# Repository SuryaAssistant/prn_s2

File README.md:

<!-- Title -->
<span align = "center">

# PRN
  <b>Bidirectional SMPS Inverter</b>

STM32 Code

September - December 2021

This repository is open to copy for Educational purpose only and not for commercial use

</span>
<!-- End of Title -->

## Warning
The code and OpenHantek software are produced in Linux OS computer. We recommend you to use or edit the code in Linux computer for compatibility purpose. Nevertheless, you still can use this repo in Windows computer with some configuration but not for OpenHantek.

## Brief Overview of The Repository
This repository is used to save and documenting the development of bidirectional SMPS inverter project. The project was took place in Instrumentation and Control Laboratory, Universitas Sebelas Maret.

## Prequerities
Yout need to have this software before use this repository
- STM32CubeIDE v1.6.1 or above. Link : https://www.st.com/en/development-tools/stm32cubeide.html
- OpenHantek6022 (Linux). Link : https://github.com/OpenHantek/OpenHantek6022
- Autodesk Eagle v9.3.0 or above (Linux or Windows). Link : https://www.autodesk.com/products/eagle/free-download

## How To Use (Linux)
From Terminal, clone this repository to your folder
```
git clone https://github.com/SuryaAssistant/prn_s2
```

Open STM32CubeIDE and then open project `prn_s2.ioc` in `stm32` folder.

The main code is saved in `stm32/Core/Src/main.c`.

## How To Use (Windows)
Download this repository by clicking green button in right-top of repository.

Extract the zip file and then move the `stm32` folder into <b>STM32CubeIDE workspace</b> in (usually) `C:\Users\{Your_Computer_Name}\STM32CubeIDE\{Your_Workspace_Name}\`.

## Clock Configuration
<span align="center">

</span>

## Pinout
<span align="center">

</span>

## Further Information
- Read the STM32CubeIDE timer and ADC configuration in https://github.com/SuryaAssistant/prn_s2/tree/main/tutorial
- Read SPWM specific configuration in https://github.com/SuryaAssistant/prn_s2/tree/main/spwm
- PCB schematic and board Design Documentation in https://github.com/SuryaAssistant/prn_s2/tree/main/pcb

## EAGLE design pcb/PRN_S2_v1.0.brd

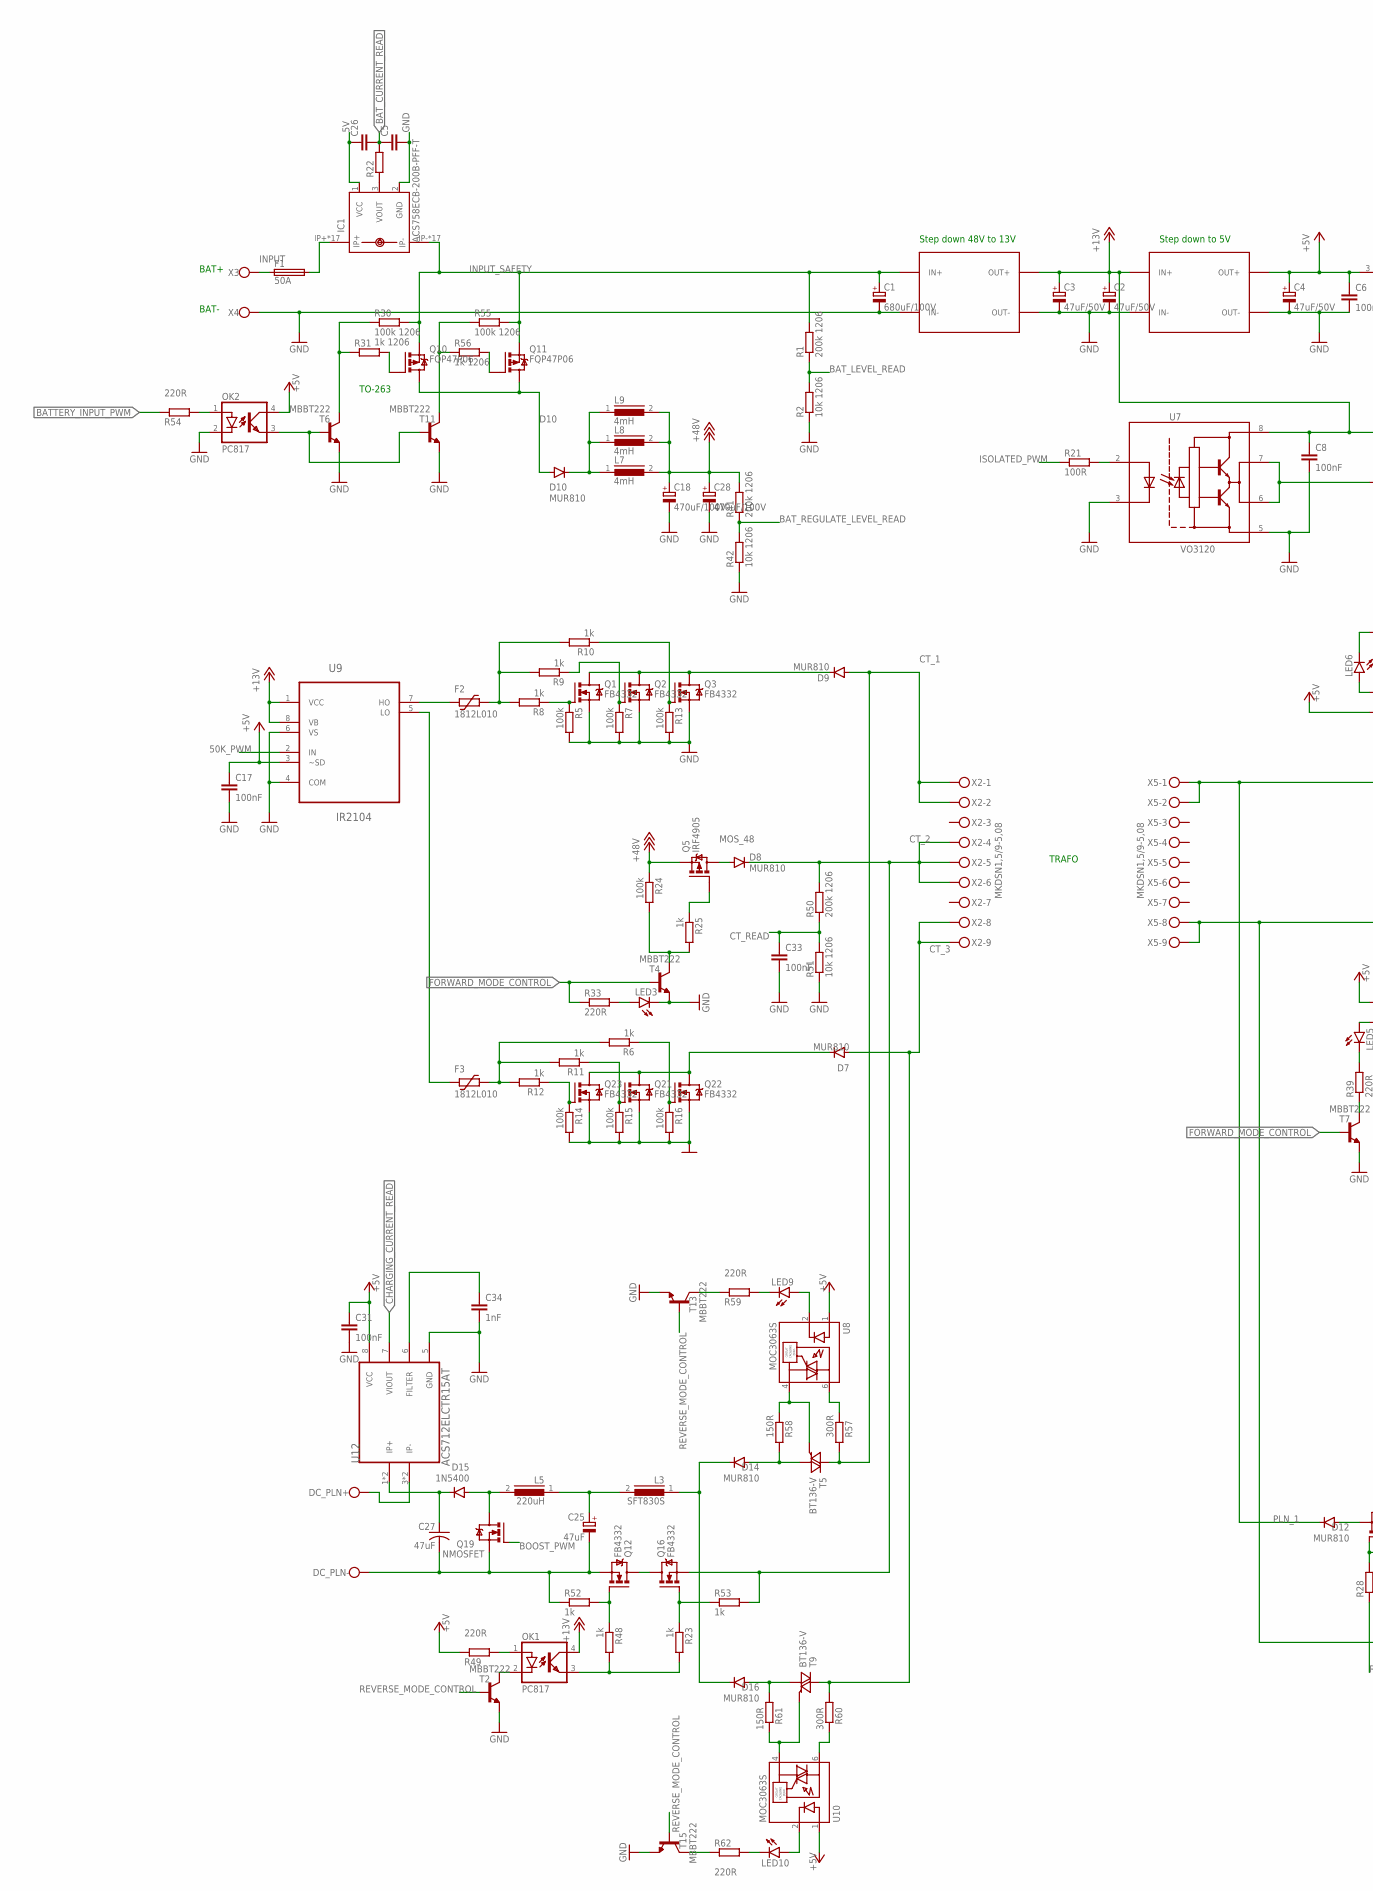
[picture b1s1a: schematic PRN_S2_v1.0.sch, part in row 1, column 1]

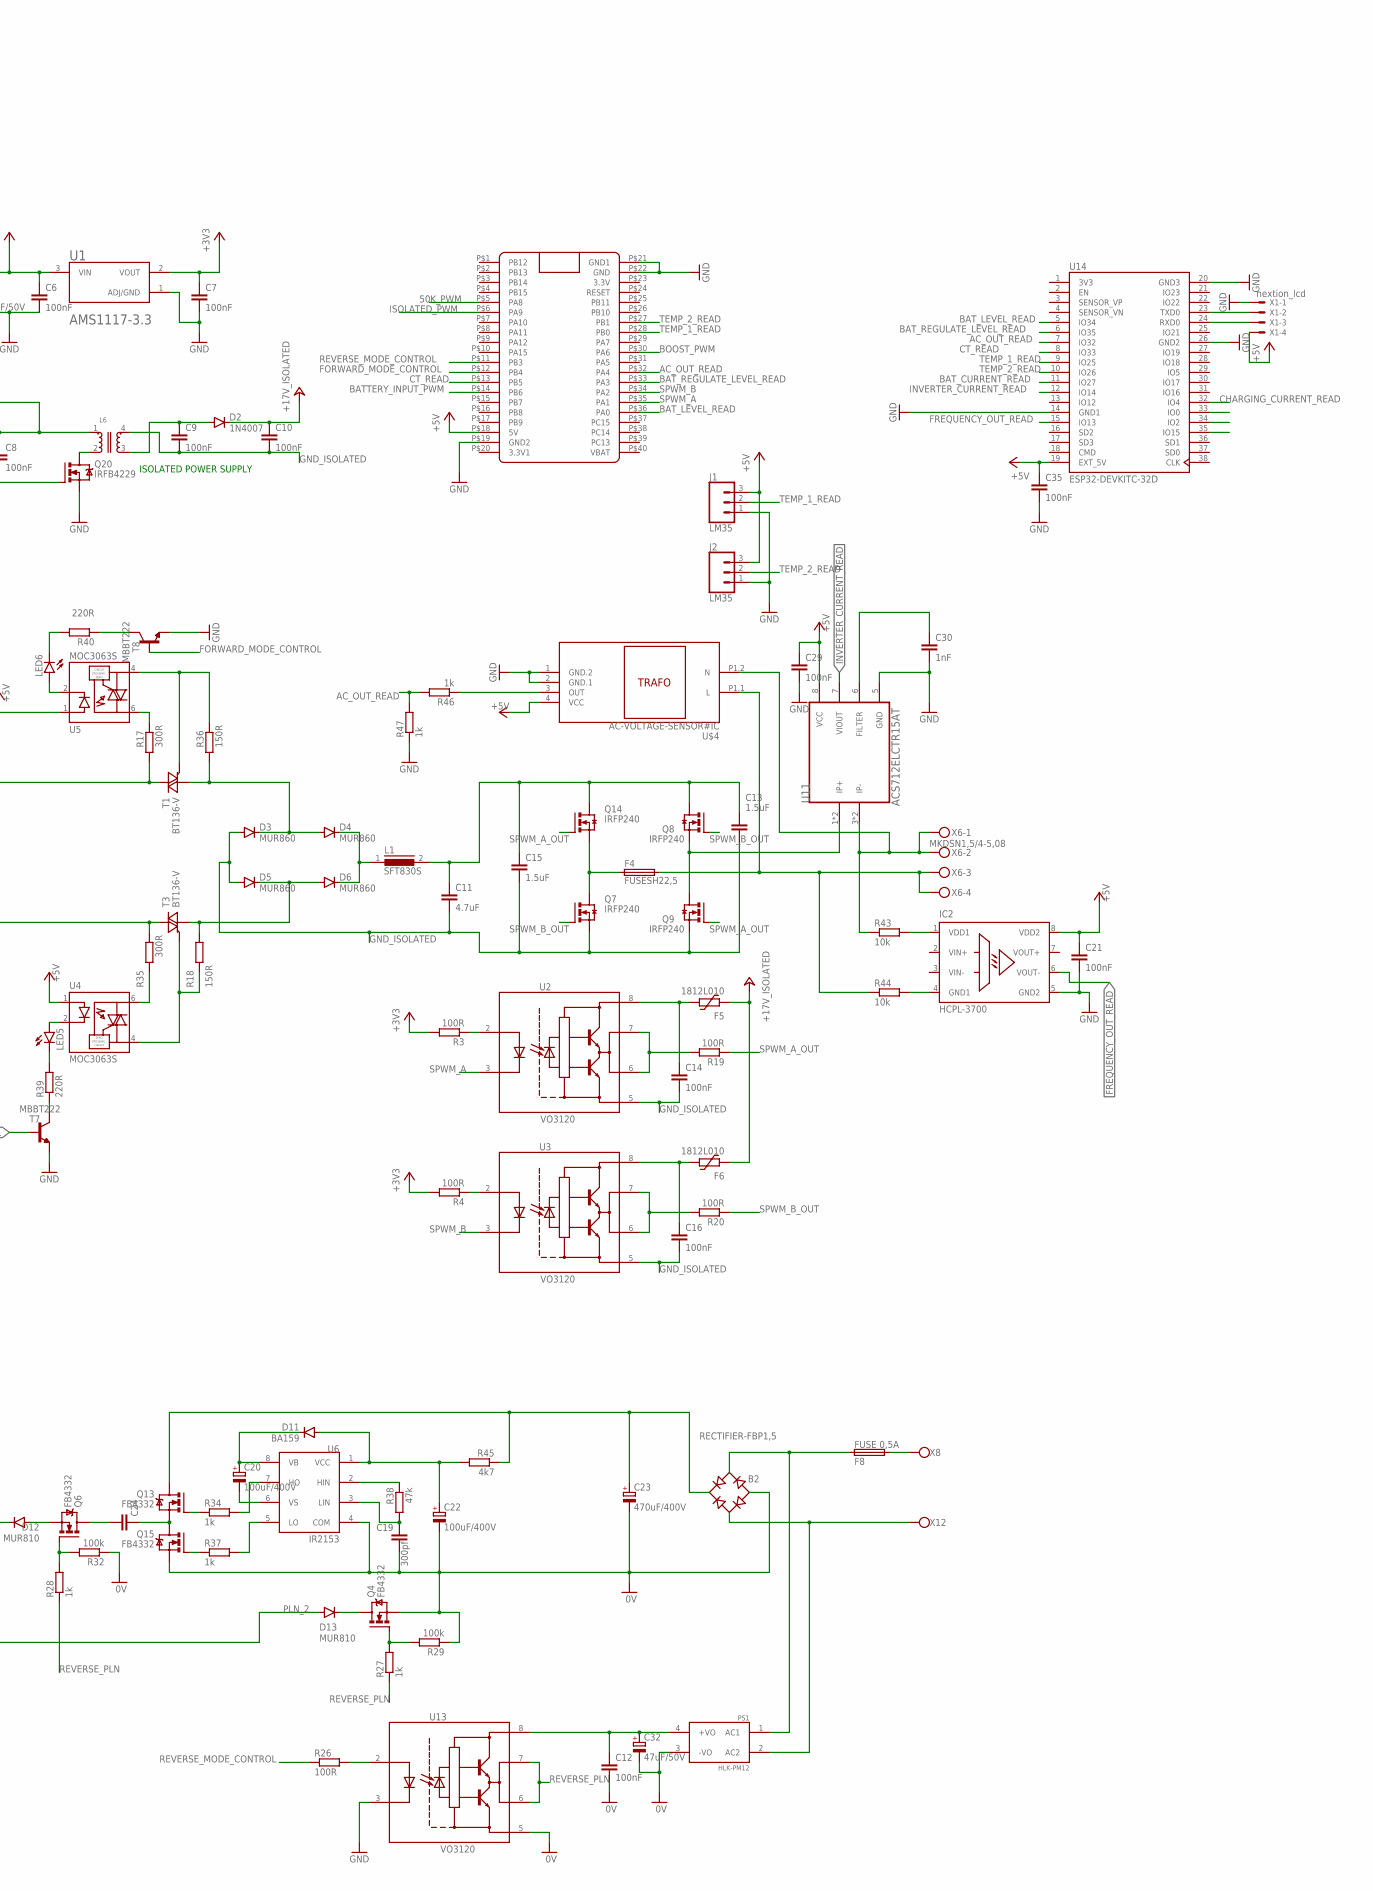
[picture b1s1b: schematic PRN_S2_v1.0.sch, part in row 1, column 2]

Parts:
B2: RECTIFIER-FBP1,5; FBP1,5
C1: 680uF/100V; E7,5-18
C2, C3, C4, C32: 47uF/50V; E2,5-6
C5, C26: CC0603; C0603
C6, C7, C14, C16, C17, C21, C29, C31, C35: 100nF; C0805K
C8, C9, C10, C12, C33: 100nF; C050-025X075
C11: 4.7uF; C275-113X316
C13, C15: 1.5uF; C150-091X182
C18, C28: 470uF/100V; E7,5-18
C19: 300pf; C0805
C20, C22: 100uF/400V; E7,5-18
C23: 470uF/400V; EB35D
C24: C-EU325-137X374; C325-137X374
C25: 47uF; E7,5-18
C27: 47uF; C050-050X075
C30, C34: 1nF; C0805K
D2: 1N4007; DO41-10
D3, D4, D5, D6: MUR860; TO220ACS
D7, D8, D9, D10, D12, D13, D14, D16: MUR810; TO220ACS
D11: BA159; DO41-10
D15: 1N5400; DO201-15
DC_PLN+: W237-112
DC_PLN-: W237-112
F1: 50A; GSH15
F2, F3, F5, F6: 1812L010; 1812L
F4: FUSESH22,5; SH22,5
F8: FUSE 0,5A; SH22,5
IC1: ACS758ECB-200B-PFF-T; CB-PFF
IC2: HCPL-3700; DIL08
J1, J2: LM35; 1X03
L1, L3: SFT830S
L5: 220uH; SFT830S
L6: WE-AMT_750082107
L7, L8, L9: 4mH; SFT830S
LED3, LED5, LED6, LED9, LED10: LEDCHIPLED_0805; CHIPLED_0805
OK1, OK2: PC817; DIL04
PS1: HLK-PM12; CONV_HLK-PM03
Q1, Q2, Q3, Q4, Q6, Q12, Q13, Q15, Q16, Q21, Q22, Q23: FB4332; TO220BV
Q5: IRF4905; TO220BV
Q7, Q8, Q9, Q14: IRFP240; TO247BV
Q10, Q11: FQP47P06; TO220BV
Q19: NMOSFET; TO220BV
Q20: IRFB4229; TO220BV
R1, R41, R50: 200k 1206; R1206
R2, R42, R51: 10k 1206; R1206
R3, R4, R19, R20, R21, R26: 100R; R0805
R5, R7, R13, R14, R15, R16, R24, R29, R32: 100k; R0805
R6, R8, R9, R10, R11, R12, R23, R25, R27, R28, R48, R52, R53: 1k; R0805
R17, R35, R57, R60: 300R; 0207/15
R18, R36, R58, R61: 150R; 0207/15
R22: RR0603; R0603
R30, R55: 100k 1206; R1206
R31, R56: 1k 1206; R1206
R33, R39, R40, R49, R54, R59, R62: 220R; R0805
R34, R37: 1k; 0207/12
R38: 47k; 0617/17
R43, R44: 10k; 0207/12
R45: 4k7; 0617/17
R46, R47: 1k; R1206
T1, T3, T5, T9: BT136-V; TO220BV
T2, T4, T6, T7, T8, T11, T13, T15: MBBT222; SOT23-EBC
U1: AMS1117-3.3; SOT229P700X180-4N
U2, U3, U7, U13: VO3120; DIP762W50P254L977H451Q8
U4, U5, U8, U10: MOC3063S; DIP762W50P254L730H500Q6
U6: IR2153; DIL08
U9: IR2104; DIP254P762X533-8
U11, U12: ACS712ELCTR15AT; SOIC127P600X175-8N
U14: ESP32-DEVKITC-32D; MODULE_ESP32-DEVKITC-32D
U$1, U$2: DC-DC-STEP-DOWN-LM2596
U$3: BLUE_PILL
U$4: AC-VOLTAGE-SENSOR#IC
X1: nextion_lcd; 22-23-2041
X2, X5: MKDSN1,5/9-5,08
X3, X4, X8, X12: W237-112
X6: MKDSN1,5/4-5,08

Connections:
0V: B2.-, C12.2, C19.2, C22.-, C23.-, C32.-, PS1.3 (-VO), Q4.S, Q15.S, R29.1, R32.1, U6.4 (COM), U13.5 (VEE)
3V3: U14.1 (3V3)
5V: C26.1, IC1.1 (VCC)
50K_PWM: U9.2 (IN), U$3.P$5 (PA8)
+3V3: C7.1, R3.2, R4.2, U1.2 (VOUT)
+5V: C4.+, C6.1, C17.1, C21.1, C29.1, C31.1, C35.1, IC2.8 (VDD2), J1.3, J2.3, OK2.4 (COL), R49.1, U1.3 (VIN), U4.1 (ANODE), U5.1 (ANODE), U8.1 (ANODE), U9.3 (~SD), U10.1 (ANODE), U11.8 (VCC), U12.8 (VCC), U14.19 (EXT_5V), U$2.OUT+, U$3.P$18 (5V), U$4.4 (VCC), X1.4
+12V: C2.+, C3.+, C8.1, L6.1, OK1.4 (COL), U7.8 (VCC), U9.1 (VCC), U9.8 (VB), U$1.OUT+, U$2.IN+
+18V: C18.+, C28.+, L7.2, L8.2, L9.2, Q5.S, R24.1, R41.2
+24V: C10.1, D2.C, F5.2, F6.2
A: D9.C, Q1.D, Q2.D, Q3.D
AC_OUT_READ: R46.2, R47.2, U14.7 (IO32), U$3.P$32 (PA4)
AFTER_D10: D10.C, L7.1, L8.1, L9.1
B: D7.C, Q21.D, Q22.D, Q23.D
BATTERY_INPUT_PWM: R54.1, U$3.P$14 (PB6)
BAT_CURRENT_READ: C5.1, C26.2, R22.2, U14.11 (IO27)
BAT_LEVEL_READ: R1.1, R2.2, U14.5 (IO34), U$3.P$36 (PA0)
BAT_REGULATE_LEVEL_READ: R41.1, R42.2, U14.6 (IO35), U$3.P$33 (PA3)
BOOST_PWM: Q19.G, U$3.P$30 (PA6)
CHARGING_CURRENT_READ: U12.7 (VIOUT), U14.32 (IO4)
CT_1: D9.A, R57.1, T5.T2 (A2), X2.1, X2.2
CT_2: D8.C, Q16.S, R50.2, R53.2, X2.4, X2.5, X2.6
CT_3: D7.A, R60.1, T9.T2 (A2), X2.8, X2.9
CT_READ: C33.1, R50.1, R51.2, U14.8 (IO33), U$3.P$13 (PB5)
D10: D10.A, Q10.D, Q11.D
DC_PLN: C27.1, D15.C, U12.1 (IP+), U12.2 (IP+)
DC_PLN+: DC_PLN+.1, U12.3 (IP-), U12.4 (IP-)
DC_PLN-: C25.-, C27.2, DC_PLN-.1, Q12.S, Q19.S, R52.1
FORWARD_MODE_CONTROL: R33.1, T4.B, T7.B, T8.B, U$3.P$12 (PB4)
FREQUENCY_OUT_READ: IC2.6 (VOUT-), U14.15 (IO13)
GG: OK2.3 (EMIT), T6.B, T11.B
GND: C1.-, C2.-, C3.-, C4.-, C5.2, C6.2, C7.2, C8.2, C17.2, C18.-, C21.2, C28.-, C29.2, C30.2, C31.2, C33.2, C34.2, C35.2, IC1.2 (GND), IC2.5 (GND2), J1.1, J2.1, LED3.C, OK2.2 (C), Q1.S, Q2.S, Q3.S, Q20.S, Q21.S, Q22.S, Q23.S, R2.1, R5.2, R7.2, R13.2, R14.2, R15.2, R16.2, R42.1, R47.1, R51.1, T2.E, T4.E, T6.E, T7.E, T8.E, T11.E, T13.E, T15.E, U1.1 (ADJ/GND), U7.3 (C), U7.5 (VEE), U9.4 (COM), U9.6 (VS), U11.5 (GND), U12.5 (GND), U13.3 (C), U14.14 (GND1), U14.20 (GND3), U14.26 (GND2), U$1.IN-, U$1.OUT-, U$2.IN-, U$2.OUT-, U$3.P$19 (GND2), U$3.P$21 (GND1), U$3.P$22 (GND), U$4.1 (GND.2), U$4.2 (GND.1), X1.1, X4.1
GND_ISOLATED: C9.2, C10.2, C11.2, C13.2, C14.2, C15.2, C16.2, D3.A, D5.A, L6.4 (2), Q7.S, Q9.S, U2.5 (VEE), U3.5 (VEE)
INPUT: F1.1, X3.1
INPUT_SAFETY: C1.+, IC1.IP-, IC1.IP-@2 (IP-), IC1.IP-@3 (IP-), IC1.IP-@4 (IP-), IC1.IP-@5 (IP-), IC1.IP-@6 (IP-), IC1.IP-@7 (IP-), IC1.IP-@8 (IP-), IC1.IP-@9 (IP-), IC1.IP-@10 (IP-), IC1.IP-@11 (IP-), IC1.IP-@12 (IP-), IC1.IP-@13 (IP-), IC1.IP-@14 (IP-), IC1.IP-@15 (IP-), IC1.IP-@16 (IP-), IC1.IP-@17 (IP-), Q10.S, Q11.S, R1.2, R30.2, R55.2, U$1.IN+
INVERTER_CURRENT_READ: U11.7 (VIOUT), U14.12 (IO14)
IN_48V: F1.2, IC1.IP+, IC1.IP+@2 (IP+), IC1.IP+@3 (IP+), IC1.IP+@4 (IP+), IC1.IP+@5 (IP+), IC1.IP+@6 (IP+), IC1.IP+@7 (IP+), IC1.IP+@8 (IP+), IC1.IP+@9 (IP+), IC1.IP+@10 (IP+), IC1.IP+@11 (IP+), IC1.IP+@12 (IP+), IC1.IP+@13 (IP+), IC1.IP+@14 (IP+), IC1.IP+@15 (IP+), IC1.IP+@16 (IP+), IC1.IP+@17 (IP+)
ISOLATED_PWM: R21.1, U$3.P$6 (PA9)
MOS_48: D8.A, Q5.D
unnamed: Q5.G, R25.1
unnamed: Q20.G, U7.6 (VO1), U7.7 (VO2)
unnamed: L6.2 (4), Q20.D
unnamed: Q10.G, R31.2
unnamed: Q11.G, R56.2
unnamed: IC1.3 (VOUT), R22.1
unnamed: F2.1, R8.2, R9.2, R10.2
unnamed: C9.1, D2.A, L6.3
unnamed: Q13.G, R34.1
unnamed: LED3.A, R33.2
unnamed: F3.1, R6.2, R11.2, R12.2
unnamed: Q2.G, R7.1, R9.1
unnamed: Q21.G, R11.1, R15.1
unnamed: Q22.G, R6.1, R16.1
unnamed: R46.1, U$4.3 (OUT)
unnamed: C30.1, U11.6 (FILTER)
unnamed: U14.23 (TXD0), X1.2
unnamed: R17.2, U5.6 (MAIN_TERM1)
unnamed: R18.1, T3.G, U4.4 (MAIN_TERM2)
unnamed: D13.C, Q4.D
unnamed: R36.2, T1.G, U5.4 (MAIN_TERM2)
unnamed: D3.C, D4.A, R36.1, T1.T1 (A1)
unnamed: C14.1, F5.1, U2.8 (VCC)
unnamed: D4.C, D6.C, L1.1
unnamed: D5.C, D6.A, R18.2, T3.T1 (A1)
unnamed: R19.2, U2.6 (VO1), U2.7 (VO2)
unnamed: C34.1, U12.6 (FILTER)
unnamed: F4.1, Q7.D, Q14.S
unnamed: C11.1, C13.1, C15.1, L1.2, Q8.D, Q14.D
unnamed: R43.1, U11.3 (IP-), U11.4 (IP-), U$4.P1.2 (N), X6.1, X6.2
unnamed: F4.2, R44.1, U$4.P1.1 (L), X6.3, X6.4
unnamed: Q8.S, Q9.D, U11.1 (IP+), U11.2 (IP+)
unnamed: LED5.A, U4.2 (CATHODE)
unnamed: R20.2, U3.6 (VO1), U3.7 (VO2)
unnamed: C16.1, F6.1, U3.8 (VCC)
unnamed: Q15.G, R37.1
unnamed: R3.1, U2.2 (A)
unnamed: R4.1, U3.2 (A)
unnamed: R21.2, U7.2 (A)
unnamed: R24.2, R25.2, T4.C
unnamed: F3.2, U9.5 (LO)
unnamed: C24.1, Q13.S, Q15.D
unnamed: Q12.G, R48.1, R52.2
unnamed: C24.2, Q6.D
unnamed: Q6.G, R28.2, R32.2
unnamed: R35.1, U4.6 (MAIN_TERM1)
unnamed: R26.2, U13.2 (A)
unnamed: OK1.2 (C), T2.C
unnamed: IC2.4 (GND1), R44.2
unnamed: F2.2, U9.7 (HO)
unnamed: Q1.G, R5.1, R8.1
unnamed: R55.1, R56.1, T11.C
unnamed: Q23.G, R12.1, R14.1
unnamed: Q4.G, R27.2, R29.2
unnamed: R30.1, R31.1, T6.C
unnamed: U14.24 (RXD0), X1.3
unnamed: LED5.C, R39.2
unnamed: Q3.G, R10.1, R13.1
unnamed: R39.1, T7.C
unnamed: LED6.A, U5.2 (CATHODE)
unnamed: LED6.C, R40.2
unnamed: R40.1, T8.C
unnamed: F8.2, X8.1
unnamed: IC2.1 (VDD1), R43.2
unnamed: C12.1, C32.+, PS1.4 (+VO), U13.8 (VCC)
unnamed: R38.1, U6.2 (HIN)
unnamed: C19.1, R38.2, U6.3 (LIN)
unnamed: C20.-, U6.6 (VS)
unnamed: D12.A, Q6.S
unnamed: Q12.D, Q16.D
unnamed: R34.2, U6.7 (HO)
unnamed: R37.2, U6.5 (LO)
unnamed: OK1.3 (EMIT), R23.2, R48.2
unnamed: B2.AC2, PS1.2 (AC2), X12.1
unnamed: B2.AC1, F8.1, PS1.1 (AC1)
unnamed: OK1.1 (A), R49.2
unnamed: B2.+, C23.+, Q13.D, R45.1
unnamed: Q16.G, R23.1, R53.1
unnamed: OK2.1 (A), R54.2
unnamed: R57.2, U8.6 (MAIN_TERM1)
unnamed: R58.2, T5.G, U8.4 (MAIN_TERM2)
unnamed: D15.A, L5.2, Q19.D
unnamed: D14.A, R58.1, T5.T1 (A1)
unnamed: D16.A, R61.1, T9.T1 (A1)
unnamed: D14.C, D16.C, L3.1
unnamed: C25.+, L3.2, L5.1
unnamed: LED9.A, U8.2 (CATHODE)
unnamed: LED9.C, R59.2
unnamed: R59.1, T13.C
unnamed: R60.2, U10.6 (MAIN_TERM1)
unnamed: R61.2, T9.G, U10.4 (MAIN_TERM2)
unnamed: LED10.A, U10.2 (CATHODE)
unnamed: LED10.C, R62.2
unnamed: R62.1, T15.C
PLN_1: D12.C, R17.1, T1.T2 (A2), X5.1, X5.2
PLN_2: D13.A, R35.2, T3.T2 (A2), X5.8, X5.9
REVERSE_MODE_CONTROL: R26.1, T2.B, T13.B, T15.B, U$3.P$11 (PB3)
REVERSE_PLN: R27.1, R28.1, U13.6 (VO1), U13.7 (VO2)
SPWM_A: U2.3 (C), U$3.P$35 (PA1)
SPWM_A_OUT: Q9.G, Q14.G, R19.1
SPWM_B: U3.3 (C), U$3.P$34 (PA2)
SPWM_B_OUT: Q7.G, Q8.G, R20.1
TEMP_1_READ: J1.2, U14.9 (IO25), U$3.P$28 (PB0)
TEMP_2_READ: J2.2, U14.10 (IO26), U$3.P$27 (PB1)
VB: C20.+, D11.C, U6.8 (VB)
VCC: C22.+, D11.A, R45.2, U6.1 (VCC)
VIN+: IC2.2 (VIN+)
VIN-: IC2.3 (VIN-)
VOUT+: IC2.7 (VOUT+)

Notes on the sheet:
BAT+
BAT-
Step down 48V to 13V
Step down to 5V
ISOLATED POWER SUPPLY
TRAFO
TO-263

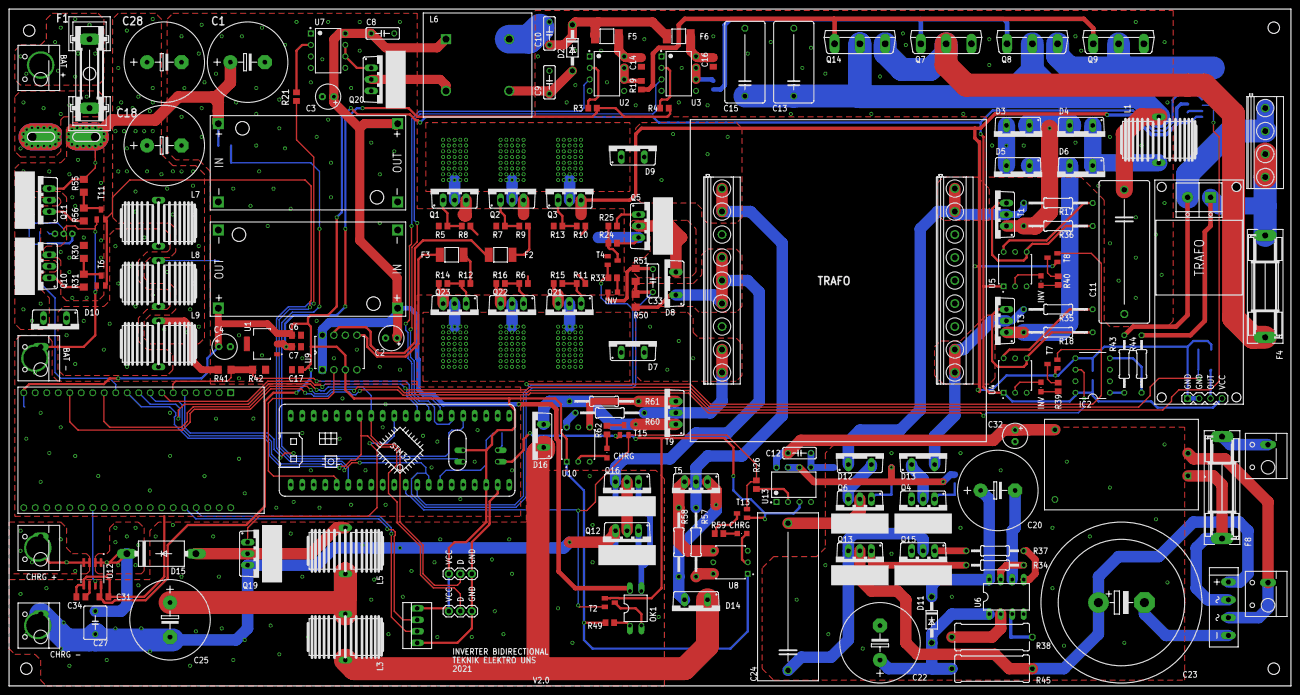
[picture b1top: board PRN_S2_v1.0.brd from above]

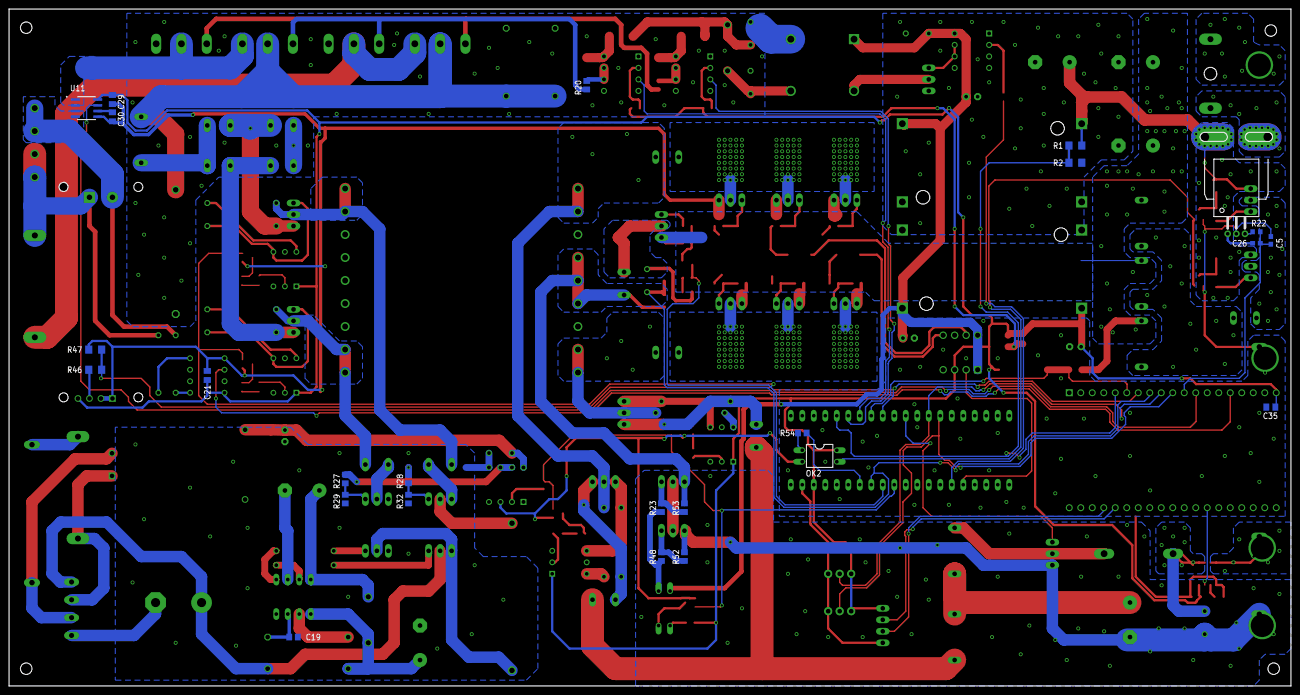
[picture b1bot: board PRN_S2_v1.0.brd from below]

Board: 2 copper layers, 283.2 x 149.5 mm, 200 parts (25 on the bottom side), 143 nets.

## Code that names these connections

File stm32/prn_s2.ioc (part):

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Mcu.Name=STM32F103C(8-B)Tx
Mcu.Package=LQFP48
Mcu.UserName=STM32F103C8Tx
PA0-WKUP.Signal=ADCx_IN0
PA1.Signal=S_TIM2_CH2
PA10.Signal=S_TIM1_CH3
PA13.Mode=Serial_Wire
PA13.Signal=SYS_JTMS-SWDIO
PA14.Mode=Serial_Wire
PA14.Signal=SYS_JTCK-SWCLK
PA2.Signal=S_TIM2_CH3
PA3.Signal=ADCx_IN3
PA4.Signal=ADCx_IN4
PA5.Signal=ADCx_IN5
PA6.Signal=S_TIM3_CH1
PA8.Signal=S_TIM1_CH1
PA9.Signal=S_TIM1_CH2
PB0.Signal=ADCx_IN8
PB1.Signal=ADCx_IN9
PB3.GPIOParameters=PinState,GPIO_PuPd,GPIO_Label
PB3.GPIO_Label=REVERSE
PB3.GPIO_PuPd=GPIO_PULLDOWN
PB3.PinState=GPIO_PIN_RESET
PB3.Signal=GPIO_Output
PB4.GPIOParameters=GPIO_PuPd,GPIO_Label
PB4.GPIO_Label=FORWARD
PB4.GPIO_PuPd=GPIO_PULLDOWN
PB4.Signal=GPIO_Output
PB6.Signal=S_TIM4_CH1
PC13-TAMPER-RTC.Signal=GPIO_Output
PD0-OSC_IN.Mode=HSE-External-Oscillator
PD0-OSC_IN.Signal=RCC_OSC_IN
PD1-OSC_OUT.Mode=HSE-External-Oscillator
PD1-OSC_OUT.Signal=RCC_OSC_OUT
RCC.SYSCLKFreq_VALUE=72000000
RCC.SYSCLKSource=RCC_SYSCLKSOURCE_PLLCLK
board=custom

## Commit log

2021-12-15 skeleton code
2021-12-21 openhantek_software
2021-12-21 stm32cubeide
2021-12-21 spwm source
2021-12-31 program
2021-12-31 general readme
2021-12-31 initial
2021-12-31 pcb files
2022-01-03 clock
2022-01-03 adc and timer
2022-01-03 further link
2022-01-03 table
2022-01-03 licence
2022-01-03 license

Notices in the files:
parts and their libraries:
EMI_FILTER: Copyright: Würth Elektronik
diy-modules: Released under the Creative Commons Attribution 4.0 International License: http://creativecommons.org/licenses/by/4.0
irf-2: Copyright & License
This library is licensed under the General Public License, Version 2.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
